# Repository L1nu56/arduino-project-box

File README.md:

# arduino-project-box
Simply a box locked by an arduino, but with some optional features for the portenta h7. The "os" directory contain the files that can directly 
edited with the Arduino IDE. The "Projekt-Box" contain technical files for the plate with the quadruple Half-H Driver.

The [README](https://github.com/L1nu56/arduino-project-box/Projekt-Box/README.md) in the Projekt-Box directory list the steps to install the hardware.

## 1. Requisites
  Ref | Value               | Part                           | Footprint                  | Description                            | Vendor
  ----|---------------------|--------------------------------|----------------------------|----------------------------------------|----------
  J1  | I2C-Conn            | Connector:Conn_01x04_Female    |                            | Generic connector, single row, 01x04   | 
  J1  | I2C-Conn            | Connector:Conn_01x04_Female    |                            | Generic connector, single row, 01x04   | 
  J1  | I2C-Conn            | Connector:Conn_01x04_Female    |                            | Generic connector, single row, 01x04   | 
  J1  | I2C-Conn            | Connector:Conn_01x04_Female    |                            | Generic connector, single row, 01x04   | 
  J1  | I2C-Conn            | Connector:Conn_01x04_Female    |                            | Generic connector, single row, 01x04   | 
  J1  | PWR-Conn            | Connector:Conn_01x04_Female    |                            | Generic connector, single row, 01x04   | 
  J1  | MOTOR-Conn          | Connector:Conn_01x04_Female    |                            | Generic connector, single row, 01x04   | 
  J1  | PWM-Conn            | Connector:Conn_01x04_Female    |                            | Generic connector, single row, 01x02   | 
  Q1  | Q_NPN_BCE           | Device:Q_NPN_BCE               |                            | NPN transistor, base/collector/emitter | 
  Q1  | Q_NPN_BCE           | Device:Q_NPN_BCE               |                            | NPN transistor, base/collector/emitter | 
  R1  | 1K                  | Device:R                       |                            | Resistor                               | 
  R1  | 1K                  | Device:R                       |                            | Resistor                               | 
  R1  | 10K                 | Device:R                       |                            | Resistor                               | 
  R1  | 10K                 | Device:R                       |                            | Resistor                               | 
  M1  | STEPPER MOTOR       | Motor:Stepper_Motor_bipolar    |                            | Bipolar stepper motor                  | 
  U1  | L293D               | Driver_Motor:L293D             | Package_DIP:DIP-16_W7.62mm |	Quadruple Half-H Drivers               | ST / TI
  U2  | Arduino Portenta h7 | Device_MCU:Arduino_Portenta_h7 |                            | Microcontroller  Arduino               | Arduino
  U3  | SCD30               | Sensor:SCD30                   |                            | CO2 Sensor                             | Sensirion
  U4  | LCM1602             | Driver_LCD:LCM1602             |                            | LC Display Driver                      | YwRobot
  U4  |                     | Device:                        |                            | Numeric Keypad                         |

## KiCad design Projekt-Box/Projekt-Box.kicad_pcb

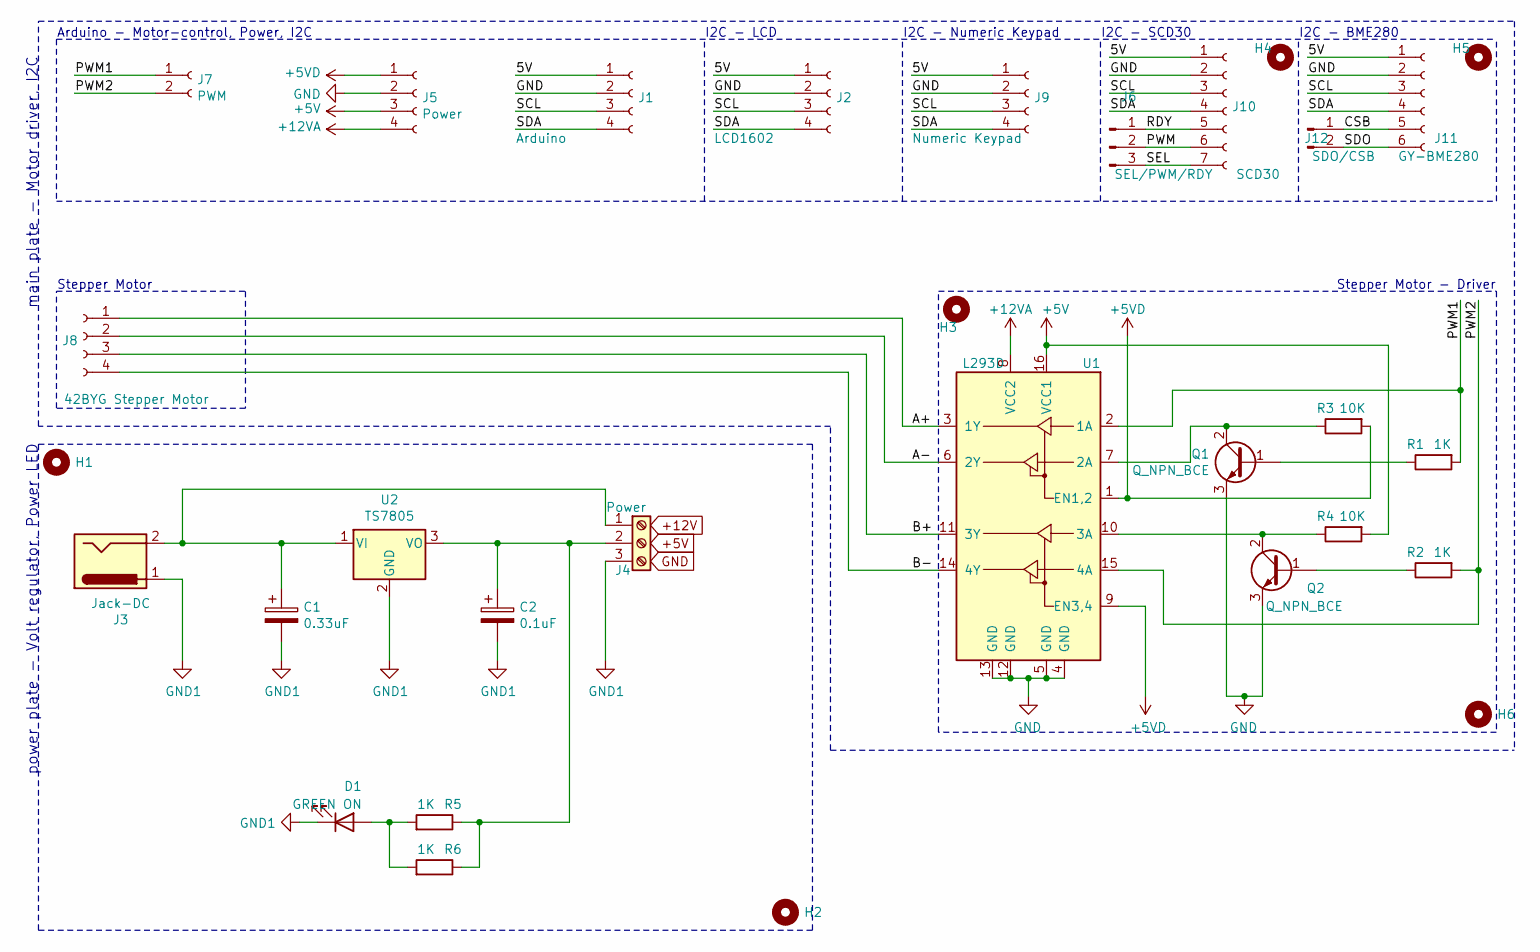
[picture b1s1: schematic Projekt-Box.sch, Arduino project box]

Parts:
C1: 0.33uF; CP_Radial_Tantal_D5.0mm_P2.50mm
C2: 0.1uF; CP_Radial_Tantal_D4.5mm_P2.50mm
D1: GREEN ON; LED_D3.0mm
H1: MP1_Power-plate; MountingHole_2.2mm_M2_DIN965
H2: MP2_power-plate; MountingHole_2.2mm_M2_DIN965
H3: MP1-1_main-plate--motor-driver; MountingHole_2.2mm_M2_DIN965
H4: MP2-1-main-plate--I2C; MountingHole_2.2mm_M2_DIN965
H5: MP2-1_main-plate--I2C; MountingHole_2.2mm_M2_DIN965
H6: MP1-2_main-plate--motor-driver; MountingHole_2.2mm_M2_DIN965
J1: Arduino; PinHeader_1x04_P2.54mm_Vertical
J2: LCD1602; PinHeader_1x04_P2.54mm_Vertical
J3: Jack-DC; BarrelJack_CUI_PJ-063AH_Horizontal
J4: Power; TerminalBlock_MetzConnect_Type011_RT05503HBWC_1x03_P5.00mm_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
J5: Power; PinHeader_1x04_P2.54mm_Vertical
J6: SEL/PWM/RDY; PinHeader_1x03_P2.54mm_Vertical
J7: PWM; PinHeader_1x02_P2.54mm_Vertical
J8: 42BYG Stepper Motor; PinHeader_1x04_P2.54mm_Vertical
J9: Numeric Keypad; PinHeader_1x04_P2.54mm_Vertical
J10: SCD30; PinHeader_1x07_P2.54mm_Vertical
J11: GY-BME280; PinHeader_1x06_P2.54mm_Vertical
J12: SDO/CSB; PinHeader_1x02_P2.54mm_Vertical
Q1, Q2: Q_NPN_BCE; TO-92
R1, R2, R5, R6: 1K; R_Axial_DIN0204_L3.6mm_D1.6mm_P5.08mm_Horizontal
R3, R4: 10K; R_Axial_DIN0204_L3.6mm_D1.6mm_P5.08mm_Horizontal
U1: L293D; DIP-16_W7.62mm
U2: TS7805; TO-220-3_Vertical

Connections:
+5V: J5.3, R4.2, U1.16 (VCC1)
+5VD: J5.1, R3.2, U1.1 (EN1,2), U1.9 (EN3,4)
+12VA: J5.4, U1.8 (VCC2)
/5V: J1.1, J2.1, J9.1, J10.1, J11.1
/A+: J8.1, U1.3 (1Y)
/A-: J8.2, U1.6 (2Y)
/B+: J8.3, U1.11 (3Y)
/B-: J8.4, U1.14 (4Y)
/CSB: J11.5, J12.1
/PWM: J6.2, J10.6
/PWM1: J7.1, R1.2, U1.2 (1A)
/PWM2: J7.2, R2.2, U1.15 (4A)
/RDY: J6.1, J10.5
/SCL: J1.3, J2.3, J9.3, J10.3, J11.3
/SDA: J1.4, J2.4, J9.4, J10.4, J11.4
/SDO: J11.6, J12.2
/SEL: J6.3, J10.7
GND: J1.2, J2.2, J5.2, J9.2, J10.2, J11.2, Q1.3 (E), Q2.3 (E), U1.4 (GND), U1.5 (GND), U1.12 (GND), U1.13 (GND)
GND1: C1.2, C2.2, D1.1 (K), J3.1, J4.3, U2.2 (GND)
unnamed: C1.1, J3.2, J4.1, U2.1 (VI)
unnamed: C2.1, J4.2, R5.1, R6.1, U2.3 (VO)
unnamed: D1.2 (A), R5.2, R6.2
unnamed: Q1.1 (B), R1.1
unnamed: Q1.2 (C), R3.1, U1.7 (2A)
unnamed: Q2.1 (B), R2.1
unnamed: Q2.2 (C), R4.1, U1.10 (3A)

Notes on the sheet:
Arduino - Motor-control, Power, I2C
I2C - LCD
I2C - Numeric Keypad
I2C - SCD30
I2C - BME280
Stepper Motor
Stepper Motor - Driver
main plate - Motor driver, I2C
power plate - Volt regulator, Power LED

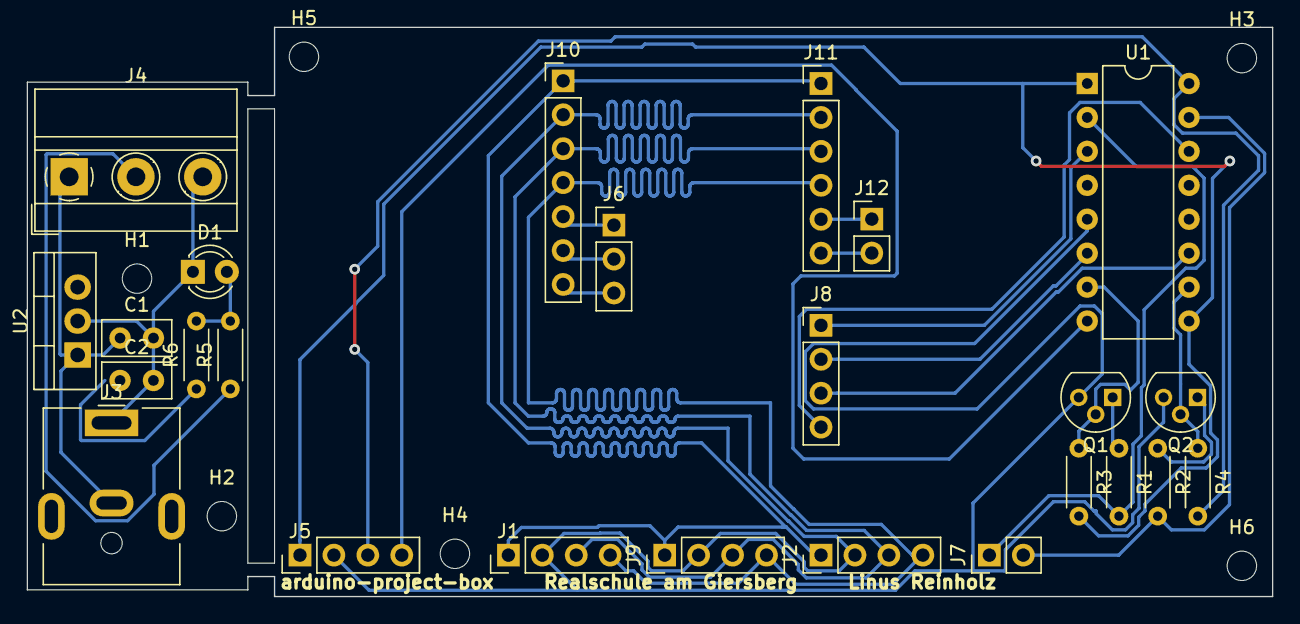
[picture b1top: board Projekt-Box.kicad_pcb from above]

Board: 2 copper layers, 93.2 x 42.6 mm, 31 parts (0 on the bottom side), 26 nets.

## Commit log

2021-03-13 Update README.md
    Add requisites
2021-03-13 Upload my existing work
2021-03-13 Add technical files
2021-03-13 Update accesspoint.h
    Add classes and functions
2021-03-13 Update ap-MAKROS.h
    Add libraries
2021-03-15 Add files via upload
    Add voarious status codes
2021-03-19 Update README.md
    Add a link and two vendors
